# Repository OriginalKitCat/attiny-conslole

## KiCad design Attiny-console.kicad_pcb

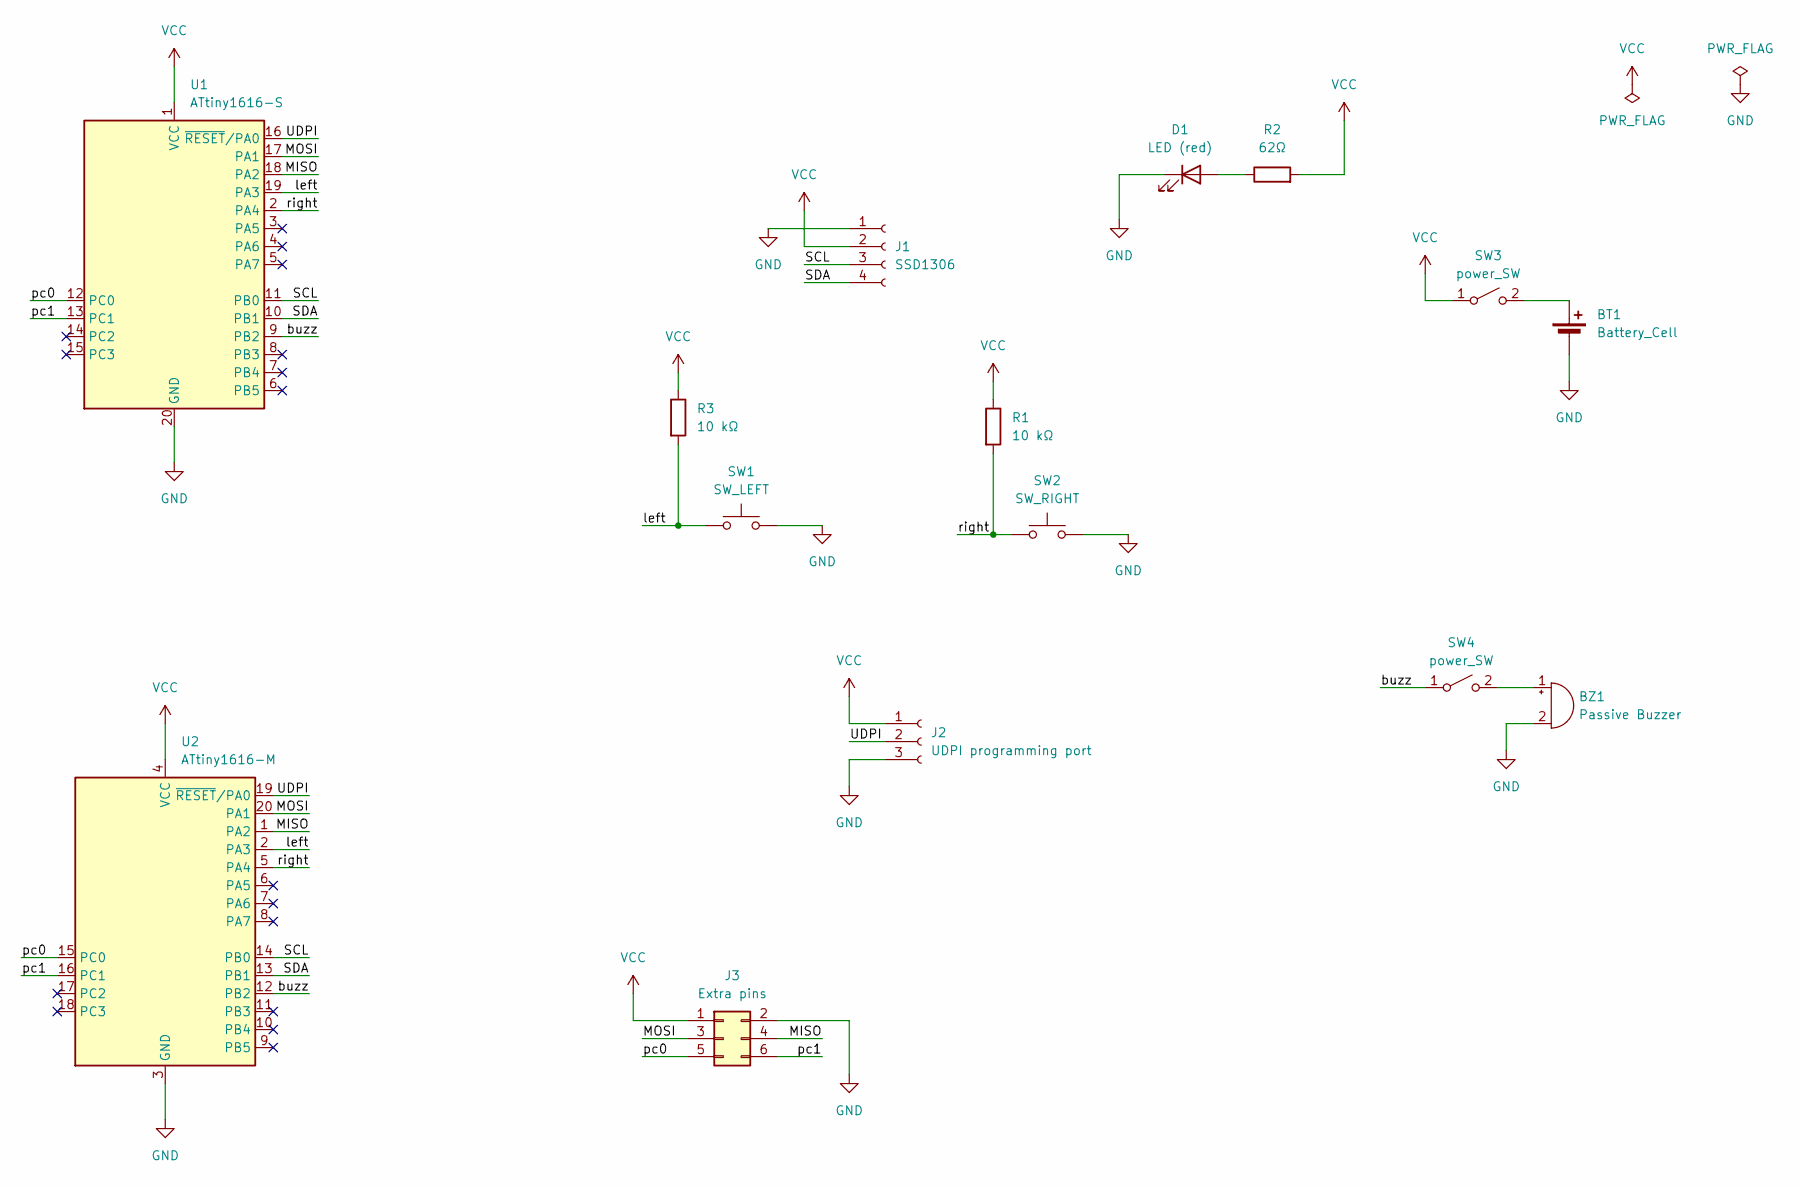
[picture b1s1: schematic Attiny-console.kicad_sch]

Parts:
BT1: Battery_Cell; BatteryHolder_Keystone_1060_1x2032
BZ1: Passive Buzzer; MagneticBuzzer_Kobitone_254-EMB84Q-RO
D1: LED (red); LED_0603_1608Metric_Pad1.05x0.95mm_HandSolder
J1: SSD1306; PinSocket_1x04_P2.54mm_Vertical
J2: UDPI programming port; PinSocket_1x03_P2.54mm_Horizontal
J3: Extra pins; PinSocket_2x03_P2.54mm_Vertical
R1, R3: 10 kΩ; R_Axial_DIN0207_L6.3mm_D2.5mm_P7.62mm_Horizontal
R2: 62Ω; R_0805_2012Metric_Pad1.20x1.40mm_HandSolder
SW1: SW_LEFT; SW_PUSH_6mm
SW2: SW_RIGHT; SW_PUSH_6mm
SW3, SW4: power_SW; SW_Slide_SPDT_Angled_CK_OS102011MA1Q
U1: ATtiny1616-S; SOIC-20W_7.5x12.8mm_P1.27mm
U2: ATtiny1616-M; VQFN-20-1EP_3x3mm_P0.4mm_EP1.7x1.7mm

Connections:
/MISO: J3.4, U1.18 (PA2), U2.1 (PA2)
/MOSI: J3.3, U1.17 (PA1), U2.20 (PA1)
/SCL: J1.3, U1.11 (PB0), U2.14 (PB0)
/SDA: J1.4, U1.10 (PB1), U2.13 (PB1)
/UDPI: J2.2, U1.16 (~RESET/PA0), U2.19 (~RESET/PA0)
/buzz: SW4.1 (A), U1.9 (PB2), U2.12 (PB2)
/left: R3.2, SW1.1, U1.19 (PA3), U2.2 (PA3)
/pc0: J3.5, U1.12 (PC0), U2.15 (PC0)
/pc1: J3.6, U1.13 (PC1), U2.16 (PC1)
/right: R1.2, SW2.1, U1.2 (PA4), U2.5 (PA4)
GND: BT1.2 (-), BZ1.2 (-), D1.1 (K), J1.1, J2.3, J3.2, SW1.2, SW2.2, U1.20 (GND), U2.3 (GND), U2.21 (GND)
unnamed: BT1.1 (+), SW3.2 (B)
unnamed: BZ1.1 (+), SW4.2 (B)
unnamed: D1.2 (A), R2.1
VCC: J1.2, J2.1, J3.1, R1.1, R2.2, R3.1, SW3.1 (A), U1.1 (VCC), U2.4 (VCC)

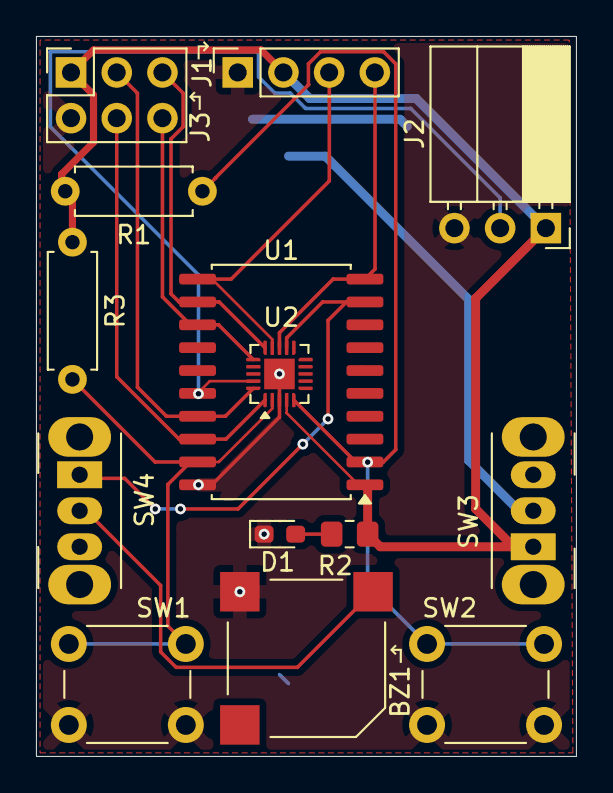
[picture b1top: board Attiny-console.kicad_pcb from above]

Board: 2 copper layers, 30.0 x 40.0 mm, 15 parts (1 on the bottom side), 15 nets.

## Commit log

2026-06-01 Adding kicad files to repo
2026-06-02 The layout looks good now
2026-06-05 Finishing the layout
2026-06-08 Starting develop the code
